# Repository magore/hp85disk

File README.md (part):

\section README

# Documentation
## HP85 Disk Emulator Copyright (C) 2014-2020 Mike Gore 
  * This Project Emulates **AMIGO** and **SS80** disk drives used by the **HP85** series computers.
  * The images are stored in **LIF** format used by the **HP85** series computers
  * See [COPYRIGHT](COPYRIGHT.md) for a full copyright notice for the project
  * Documentation created using Doxygen available at
    * https://rawgit.com/magore/hp85disk/master/doxygen/html/index.html
    * All emulated disk images are just regular files stored on a standard FAT32 formatted SD Card

## Features for the **HP85** in brief
  * **NOTE: Later sections go into more detail**
  * This project emulates **GPIB drives** and **HPGL printer**
    * Each emulated disk image is a **LIF** encoded file on a FAT32 formatted SD CARD.
    * **You MUST have the GPIB module installed in your HP85 in order to connect to the hp85disk emulator**
   * [sdcard/hpdisk.cfg](sdcard/hpdisk.cfg) fully defines each disk image on SD Card
     * Disk images are **LIF** encoded files that are compatible with **HP85A/B** and many other computers
     * Missing disk image files are created automatically if 
  * The emulator will automatically create missing **LIF** images defined in [sdcard/hpdisk.cfg](sdcard/hpdisk.cfg) on the SD CARD
  * There are disk images for **AMIGO** and **SS80** disks
    * **AMIGO** drives work with **HP85A** 
    * **SS80** drives work with **HP85B** (or **HP85A** with **PRM-85** with modified EMS and Electronic disk ROM add on board see links)
      * You may have up to 4 disks with V1 hardware and 8 with V2 hardware
  * There is a **Printer emulator** that can capture and save printer data to a time stamped file.
  * Built in command processor with lots of useful features
    * Want to translate between plain text **BASIC** files and **HP85** BASIC programs? You Can!
      * See full details later in this document
    * Access the hp85disk command processor via its USB interface and your computer with a serial terminal program
      * See full details later in this document for serial terminal configuration and finding the device port name
    * Any key press halts the emulator and waits for a user command
      * After finishing any user commend and options press the Enter/Return key to return to disk emulation
    * Type **help** for a list of top level commands
      * Each help item has its own help
      * Example: **lif help**
   * **LIF** manipulation tools are built in see later sections for details
   * Convert *TeleDisk* images into **LIF**
   * The emulator **RTC** can be used for time stamping plot files and files added into lif images

___ 

## Credits

## HP85 disk emulator V2 circuit board layout design by (C) 2018-2020 Jay Hamlin
## V2 board design - github master branch targets both old and new board by Jay Hamlin
## V2 code is now working
  * [Jay Hamlin designed this board](board/V2/releases)
  * V2 hardware adds
   * **PCB Circuit board design**
   * **GPIB BUS drivers**
     * 48Mma drive required by the GPIB spec
   * **I2C** level converters and standard Qwiic Bus interface - 3.3V
   * **RTC** clock for time stamping files added to **LIF** images, etc
   * Optional I2C LCD interface
     * work in progress
   * Advanced Hardware Reset circuit
   * Micro size SD card interface
  * [Current design files](https://github.com/magore/hp85disk/tree/master/board/releases/HP85Disk_release_03)
## V2 Pictures by Jay Hamlin

## HP85 disk emulator V1 board design (C) 2014-2020 Mike Gore
## [V1 board readme](board/V1/README.md)
  * [My original board design without **GPIB** buffers](board/V1/README.md)
  * Limited control and BUS drive power 
  * If you are using a **V1** board changes the update the [Makefile](Makefile) **BOARD ?= 1**
    * About half of the 48Mma drive required by the **GPIB** spec
    * However we can read any pin any time - useful for tracing/debugging
  * **RTC** -  **DS1307** for time stamping 

## HP Disk Emulator by Anders Gustafsson
**Anders Gustafsson was extremely helpful in getting my project started.**
*In fact I really owe the very existence of this project to his original project*
 * You can visit his project at this site:
   * <http://www.dalton.ax/hpdisk>
   * <http://www.elektor-labs.com/project/hpdisk-an-sd-based-disk-emulator-for-gpib-instruments-and-computers.13693.html>

Anders originally provided me his source code in 2014 and many details of his project *which I am very thankful for.*
NOTE: 
 I ended up rewriting virtually all of Anders project.
 This was mainly a personal exercise in fully understanding the code and NOT because of any problems with his original work.
 I did this one part at a time as I read the HP documents covering the protocols and specifications.
 Although rewritten I have maintained the basic concept of using  state machines for **GPIB** ,**AMIGO** and **SS80** state tracking.

## The HPDir project was a vital documentation source for this project
  * <http://www.hp9845.net/9845/projects/hpdir>
  * I use the **hpdir.ini** of their project for creating disk images

### Other HPDir resources for disk image manipulation
  * [HPDrive project has very useful references an tools for creating HP disk **LIF** images compatible with this project](http://www.hp9845.net/9845/projects/hpdrive)
    * Copyright © 2010 **A. Kückes**
  * [HPDir project has very useful references and tools for manipulating HP disk **LIF** images compatible with this project](http://www.hp9845.net/9845/projects/hpdrive)
    * Copyright © 2010 **A. Kückes**
  * [ See **LIF** Documentation - part of the HPDir project for details](http://www.hp9845.net/9845/projects/hpdir/#lif_filesystem)
    * Copyright © 2010 **A. Kückes**

## My TeleDisk to LIF conversion utility
 * I used the lzss libraries and documentation by **Dave Dunfield**
   * Copyright 2007-2008 Dave Dunfield All rights reserved.
 * Documentation from **Jean-Franois DEL NERO**
   * Copyright (C) 2006-2014 Jean-Franois DEL NERO
[lif/teledisk](lif/teledisk)
 * [lif/teledisk](lif/teledisk)
   * My **TELEDISK LIF** extractor
   * Important Contributions (My converted would not have been possible without these)
     * **Dave Dunfield**, LZSS Code and *TeleDisk* documentation
       * Copyright 2007-2008 Dave Dunfield All rights reserved.
       * [td0_lzss.h](lif/teledisk/td0_lzss.h)
       * [td0_lzss.c](lif/teledisk/td0_lzss.c)
         * *LZSS decoder*
       * [td0notes.txt](lif/teledisk/td0notes.txt)
         * *TeleDisk Documentation*
     * **Jean-Franois DEL NERO**, **TeleDisk Documentation**
       * Copyright (C) 2006-2014 Jean-Franois DEL NERO
         * [wteledsk.htm](lif/teledisk/wteledsk.htm)
           * *TeleDisk documentation*
         * See his github project
             * https://github.com/jfdelnero/libhxcfe

## FatFS low level disk IO
  * [fatfs](fatfs)
    * R0.14 FatFS code from (C) **ChaN**, 2019 - With very minimal changes 

## Optiboot
  * [optiboot](optiboot)
    * Optiboot Bootloader for Arduino and Atmel AVR
    * See: https://github.com/Optiboot/optiboot
       * [GPLv2 WRT](https://github.com/Optiboot/optiboot/blob/master/LICENSE)
       * [README](https://github.com/Optiboot/optiboot/blob/master/README.md)

## STK500v1 uploader for Optiboot
  * [uploader/flasher.py](uploader/flasher.py)
    * Optiboot uploader by **Mathieu Virbel** <mat@meltingrocks.com> 
      * Original repository https://github.com/tito/stk500
        * Authors main github page https://github.com/tito/stk500
          * https://meltingrocks.com/
  * Changes Jay and I made
   * Changed to atmega1284p
   * Jay converted code to Python 3
   * Added Baudrate argument
   * Added code to send "reset" command to hp85disk firmware to drop into optiboot
   * Fixed Intel 02 segment record calculation

___

## Resource Links 
  * 3D printed cases
    * https://github.com/MartinHepperle/HP-ReproParts

___

## Initial Setup of HP85 disk V2 PCB by Jay Hamlin
### Setup checklist
  * **You must an HP85 82937A GPIB card installed** [See document](Documents/82937AHP-IBInterface-InstallationAndTheoryOfOperationManual-82937-90007-56pages-Oct80)
    * **You must also have the required HP 82937A option roms installed**
      * **Mass Storage ROM** [Mass Storage ROM Manual](Documents/HP85-MassStorage.pdf)
      * **NOTE** I use the **PRM-85** with the HP85A super ROM - in my unit as it has all of the option ROMs included
  * Connect the GPIB plug from your HP85 GPIB card to the emulator - for initial testing make sure it is the only GPIB device attached
  * **NOTE:** The Emulator must be powered up and attached **before your HP85 is turned on** (the HP85 only detects disks after power-on or reset)
  * Attach the Power Supply with 2.1mm jack - suggest 7.5V to 9V DC regulated adapter with negative outside, positive center
    * You will see LED1 flash several times while the system is reading the configuration file and detecting disk images
    * If LED2 turns on there is an error reading the SD Card - see **SD Card problems** section

### Host computer requirements for serial debugging and firmware updating
  * You have either
    * **Ubuntu Linux desktop**
    * **Windows 10** running Windows Subsystem for Linux (Called WSL ) and the Ubuntu App from the Microsoft App store
    * **Mac OS**
  * All Text and configuration files used with the emulator MUST plain text format only (8 bit ASCII) 
     * Please NO Unicode - both file names and file formats!
  * You have a serial terminal program installed - for example minicom 
  * You need a FAT32 format blank SD Card
    * Copy of the hp85disk, github master branch, sdcard folder contents onto the SD Card
      * Make sure you only copy the contents and NOT folder AND contents
        * The emulator assumes the SD card home directory contains the images and configuration files

### Testing the emulator with the HP85
  * Turn on your HP85 - once the cursor is visable type the command **CAT**
    * You should see a directory listing, otherwise go to the bext section **initial troubleshooting**
  * If you have a directory listing see section called **HP85A and HP85B examples** for more examples

### Initial troubleshooting - if CAT gives a time-out error 
  * Make sure your device is the ONLY DEVICE attached to the HP 82937A controller of your HP85
  * You might not have the required option **ROMs** installed in your **HP85** for the HP85 GPIB interface card
  * The SD Card is missing the configuration file or disk images
  * The SD Card filesystem is corrupt.
  * See **SD Card problems** section
  * **NOTE** I would also suggest connecting your computer to the USB connector for more detailed disagnostics
  * USB Connection Summary
    * Attach USB cable from emulator to your computer using a serial terminal program
    * Read starting with section 
      * [Firmware updating and connecting to the hp85disk emulator with MINIMAL software install](#firmware-updating-and-connecting-to-the-hp85disk-emulator-with-minimal-software-install)
      * Read down to section [Connecting to hp85disk interactive serial port](#connecting-to-hp85disk-interactive-serial-port)
      * Read section [Command interface notes}(#command-interface-notes)
    * See section [hp85disk troubleshooting with serial terminal and DEBUG option](#hp85disk-troubleshooting-with-serial-terminal-and-debug-option) to verify your HP85 is communicating with your emulator
  * With the serial terminal connected type **help** you should see a help menu
    * To make sure there are files on the SD Card type one of these commands
      * **fatfs ls** for windows like director listing [example result](fatfs-ls.txt)  
      * **ls** for a Linux like directory listing [example result](trace/ls.txt)
  * Enter the serail terminal command **cat hpdisk.cfg** to see if you can read the main configuration file
  * Turn on debugging with the **DEBUG =** command
  * References
    * [hp85disk troubleshooting with serial terminal and DEBUG option](#hp85disk-troubleshooting-with-serial-terminal-and-debug-option)
    * [hp85disk DEBUG truth table](#hp85disk-debug-truth-table)
    * hp85disk setting debug examples](#hp85disk-setting-debug-examples)

### Status DEBUG LEDs
  * **LED2** goes on for error conditions - this is the LED nearest the GPIB connector
    * If this turns on you have an SDCARD problem - either missing card or filesystem issue
    * This LED will only go off after a reset and if no SD Card problems are detected
  * **LED1** is on when the SD Card is being read or written to

## Detailed information about tools and features 

## Built in command processor with many tools
### Accessing the hp85disk command interface with a serial terminal
  * Used to access the hp85disk command interface
  
### Command interface notes
  * When typing **any character** to the hp85disk emulator will stop disk emulation and display:
    * \<INTERRUPT>
  * After you type **Enter** the command processor will execute the command and return to disk emulation automatically

### Summary Getting files into and out of the emulator
  * The emulator uses a standard FAT32 formatted SD card accessable by standard Windows/Mac/Linux desktops.
    * This means you can removed the SD card and attach it to your desttop PC with a card reader
      * **ALWAYS POWER OFF the EMULATOR when inserting or removing the SD card**
  * Emulator disk images are single FAT32 files that are internally fomatted as LIF images - the format used by the HP85
  * This design allows you to copy files to/from the SD Card with your desktop PC
  * The hp85disk project includes tools for your desktop PC that can add/extract files from LIF disk images
    * These file and LIF image tools are also built into the emulator firmware - see references
      * [File manipulation commands built into the emulator](README.md#sd-card-file-manipulation-commands)
      * [LIF tools refrence](README.md#lif-tools-are-built-into-emulator-firmware)
      * [LIF - Importing TEXT files into LIF images](README.md#importing-ascii-and-plain-text-as-hp85-basic-programs)
      * [LIF - Exporting TEXT files from LIF images](README.md#exporting-hp85-basic-programs-to-ascii-plain-text)
      * [LIF - command](README.md#for-lif-help-type-lif-help)
    
___ 

## Important notes about SD Card requirements for the emulator

### Removing the SD Card from the emulator
  * **ALWAYS POWER OFF THE EMULATOR BEFORE REMOVING -or - INSERTING THE SD CARD**

### Formatting a new SD Card 
  * Must be formatted **FAT32** not FAT32x

### Using the SD Card images on your HP85
  * We provide the emulator with an SD card with images already installed
    * If you wish to create a new one follow these steps
  * There are working copies of disk images under the github sdcard folder
  * Open a web browser to https://github.com/magore/hp85disk
    * Click on the Green **Clone or Download** button
    * Pick download as **ZIP**
    * You can extract all of the folders and files to a folder of your choice
    * locate the **sdcard** folder
  * Copy the **contents** of the **sdcard** folder to the root/home folder of a a FAT32 formatted SD card
    * You should not see the **sdcard** folder on the SD Card itself just the contents of that folder and its subfolders

#### HP85A users SD card setup
  * Normally you will not be able to access **SS80** drives unless you have versions of the **HP85B** ROMS installed
    * See the notes about using a **PRM-85** to add the required ROMS
  * Copy the [amigo.cfg](sdcard/amigo.cfg) to the SD card and rename it to [hpdisk.cfg](sdcard/hpdisk.cfg)
    * This is an **AMIGO** drive only configuration
    * The default amigo.cfg file defines four **AMIGO** drives ready to go

#### HP85B users SD card setup
  * You needs the **EMS** ROM for **SS80** drives
    * If you do not have them see the **HP85A** notes above
  * You do not need to make any changes
    * The default [hpdisk.cfg](sdcard/hpdisk.cfg) uses two **AMIGO** drives and two **SS80** drives ready to go

___ 

###  Choosing an SD Card for the HP85 emulator PLEASE READ
  * Summary: When the hp85disk emulator writes to the SD Card the Card internally must modify a much much larger internal flash page - this can take too long
    * The **HP85** is sensitive to long read/write delays that some cards can cause problems with
    * You want SD Cards with fast random writes
    * I have found that the SanDisk Extreme and SanDisk Extreme Pro cards work best.
      * There is a huge difference in various cards on the market. 
      * Look for the cards with the best 4K random write times
      * A good source of benchmark information is looking for recent Raspberry Pi SD card benchmarks because they use SD Cards
        * Specifically look at best 4k random write - faster is better.
  * Details:
    * First step: hp85disk emulator writes to the SD Card
    * Internally the SD card finds an internal page where our data will go
    * Next the SD Card reads the page into internal RAM (recall it can be much over a megabyte)
    * Next the SD Card modifies the internal RAM with our data
    * Next the SD Card erases the page
    * Lastly the page is written to the SD Card and this takes time
      * Trivia - SD cards must to erase a page before updating because of the flash memory cell design
  * Why is this delay critical to the hp85disk emulator?
    * Too long of a delay can cause a timeout when writing to disk
    * SD cards internal hardware is mostly optimized for sequential writing 
      * Their buffers and timing are designed primarily for writing consecutive blocks one after another
        * When writing in consecutive order they can queue up many requests and combine them into one operation - a huge savings in time - done all in hardware
        * Writing to blocks in random locations break this optimization very badly
          * Therefore some SD Cards can take so long the **HP85** can timeout
      * The hp85disk emulator does not have enough memory to work around this issue
        * If we could load the entire disk image into ram AND we had more for many write buffers
          * Then we could optimize the SD Card writing process to avoid the problems
        * The AVR we use has only 20K of ram for everything
          * Perhaps some day we will port this project to a Raspberry PI with add on hardware
            * The protocol is already solved for the emulator so this would not be that hard - only a battle with the time I have free

### SD Card problems 
  * The the file system on the SD card might get corrupted if it was powered on while removing the card
    * **Symptoms - the hp85disk will not detect any drives**
      * This is because the small FatFS file system code I used can not self repair any filesystem errors
  * If you suspect this the easy way to check is to connect the emulator to a desktop/laptop computer
    * See [Firmware updating and connecting to the hp85disk emulator with MINIMAL software install](#firmware-updating-and-connecting-to-the-hp85disk-emulator-with-minimal-software-install)
  * When powering on the emulator it will report a details about the SD Card - you will see very obvious errors if it can not read the SD Card
  * If the emulator says it can not open the card then go to the **SD Card filesystem repair sections**

### SD Card filesystem repair
  * **Windows** insert the Micro SD card into you desktop/laptop Card Reader
    * Windows might detect errors and offer to fix them - answer **yes**
    * You can make Windows Check the drive using the following steps
      * Open *File Explorer* **Right Click** on the SD card drive and pick **properties**
      * Open the Tools tab
      * Click on Error Checking 
  * **Ubuntu Desktop with GUI** insert the Micro SD card into you desktop/laptop Card Reader
    * Under **Activities** search for **Disks**
      * Open **Disks** You will see a list of all of your drives on the left panel
        * Not - your SD Card may look like a USB device if you use a USB card reader
      * Click on the correct drive in the left panel
        * You will notice it give the size and partition type
      * Click on the Volume in the right panel
      * Click on the settings gear icon below the Volume
      * Click Repair filesystem
  * **Ubuntu Command line - without GUI** 
    * **sudo bash**
	* Method 1
      * Insert the Micro SD card into you desktop/laptop Card Reader
      * **dmesg | tail -25**
        * You will see the device partition listed in the last 10 or 20 lines
        * We will use: **/dev/sdc1** in the example **MAKE SURE YOU USE THE ONE YOU DETECTED**
      * **umount /dev/sdc1**
      * **fsck -f /dev/sdc1**
	* Method 2
    * **udevadm monitor --udev**
      * Insert the Micro SD card into you desktop/laptop Card Reader
      * The "add" lines will have the card partition listed on the far right
        * We will use: **/dev/sdc1** in the example **MAKE SURE YOU USE THE ONE YOU DETECTED**
      * Press **Ctrl c** to exit udevadm monitor
      * **umount /dev/sdc1**
      * **fsck -f /dev/sdc1**

___ 

## SD Card file manipulation commands 
  * **posix help** displays a list of these SD cards related commands
    * **NOTE: you do NOT have to put the "posix" keyword prior to any of these command**
  * These are very useful for backing up and copying disk images and configuration files
  * Path names may optionally be fully qualified file names or relative names
  * Directory seperators may be / or \
  * Relative names can include . or ..
    * Examples
       * .. is previous directory
       * .  is current directory
       * / or \ is a directory separator
       * /configs/../amigo0.lif is the same as /amigo0.lif
  * Note: Wild card pattern matching is NOT implemented on any of these commands.

### SD Card file command summary with examples
  * **cd dir**
    * Change to new working, default,  directory
<pre>
    cd /configs
</pre>

  * **pwd**
    * Display current working, default,  directory
<pre>
    pwd
    /configs
</pre>

  * **ls files and or directories**
    * You can specify any number of files or directory names or files as arguments
      * This is limited to a total length of 250 characters total
    * File information displayed includes type size date and name 
      * The file and directory information displayed is similar to the Linux **ls -la** command
    * Directory listing includes the file count for each directory
    * Example: 
<pre>
    ls /notes /backups /amigo0.lifg
    Listing:[/notes]
    -rwxrwxrwx none none         4151 Mon Mar  2 00:19:16 2020 drive-parameters.txt
    -rwxrwxrwx none none          563 Sun Mar  1 22:19:48 2020 GETSAVE-Readme.txt
    -rwxrwxrwx none none       367277 Sun Mar  1 22:08:44 2020 GETSAV Series80 Group Data Communications Pac for the HP 83_85.pdf
    -rwxrwxrwx none none       312128 Sun Mar  1 22:09:48 2020 GETSAV Series80 Group HP85 I_O rom Image specifier error 52.pdf
    -rwxrwxrwx none none         2560 Sun Mar  1 03:57:42 2020 GETSAVE.#e008
    -rwxrwxrwx none none         3512 Sat Feb 29 07:19:34 2020 drives_parameters.txt
    -rwxrwxrwx none none          102 Sun Mar  1 07:20:12 2020 hpdir-notes-examples.txt
    Files: 7
    Listing:[/backups]
    -rwxrwxrwx none none         3416 Fri Dec 31 19:17:44 1999 amigo.cfg
    -rwxrwxrwx none none         5690 Fri Dec 31 19:18:00 1999 hpdisk.cfg
    Files: 2
    Listing:[/amigo0.lif]
    -rwxrwxrwx none none       286720 Mon Apr 13 00:03:22 2020 amigo0.lif
    Files: 1
</pre>
  * **mkdir dir**
    * Make a new directory called dir
  * **rmdir dir**
    * Delete a directory - it must be empty
  * **rm file**
    * Remove/Delete a file
  * **copy file1 file2**
    * Copy an existing file to a new location and name
<pre>
	mkdir /backups
	copy /amigo.cfg /backups/amigo.cfg
    Opening /amigo.cfg
    Creating /backups/amigo.cfg
    
    Copying...
    3416 bytes copied.
    
    copy /hpdisk.cfg /backups/hpdisk.cfg
    Opening /hpdisk.cfg
    Creating /backups/hpdisk.cfg
    
    Copying...
    5690 bytes copied.
</pre>
  * **rename old new**
    * Rename a file - this is similar to a move command source and destination paths and names can differ
  * **page NN**
   * **NN** is the number of lines to display per page with the **cat** with the page **-p** option
   * Default is 25 lines
  * **cat file [-p]**
    * List a file to the display with optional pausing
    * **-p** page option tells **cat** to pause after the number of lines specified by the **page** command
    * When pausing, typing Space advances another page, Enter another line, q exits

___ 

## LIF tools are built into emulator firmware 
  * Built in help
    * **lif help**
      * Gives lif commands
  * Summary - List, Create, import, export, translate, copy, rename, delete, etc
  * NOTE: Each disk image is a single file, encoded in **LIF** format, saved on the SD Card
    * **LIF** format is a common the filesystem on series 80 computers.
    * **LIF** format is also a vary common file interchange format for series 80 computers
      * **LIF** format includes file date, size permissions and other important meta data
  * Translate between DTA8x (type E010) and plain text files
      * You can add a plain text file, and translate it, into a **LIF** image with file format DTA8x (type E010)
      * You can extract and translate DTA8x (type E010) into a plain text files
  * **Key LIF manipulation features**
    * **dir** display a directory of a **LIF** image
      * Directory listing of **LIF** images and SD Card files
      * If you have an RTC the listing can display file and **LIF** volume date and time
        * Display time stamps if they were set
          * But only if they were created or added with the built in tools
    * **add** an ascii file to **LIF** image
      * This function permits renaming of the translated file
      * They get translated between **HP85** DTA8x (type E010) format and plain text files!!!
    * **extract** ASCII files from **LIF** image
      * This function permits renaming of the translated file
      * They get translated between **HP85** DTA8x (type E010) format and plain text files!!!
    * **addbin** add binary programs from one **LIF** image to another *LIF* image
      * This function permits renaming of the translated file
    * **extractbin** a single binary file or program into a new **LIF** image
      * This function permits renaming of the translated file
      * Extracted **LIF** images contain a single file a 256 byte volume header, 256 byte directory followed by a file.
    * **del** delete file in **LIF** image
    * **rename** file in **LIF** image
    * **create** create a LIF image specifying a label, directory size and overall disk size
    * **createdisk** create a LIF image specifying a label and drive model name
  * [For more **LIF** documentation](lif/README.md)

## TeleDisk to LIF conversion tool (updated) - see [LIF README.md](lif/README.md)
  * [td02lif](lif/t202lif) [85-SS80.TD0](lif/85-SS80.TD0) [85-SS80.LIF](lif/85-SS80.LIF)
  * NOTE: There are a stand alone version of the tool that run on Linux - making it work on Windows should be easy
      * You can extract a **DTA8x** (type E010) file from a **LIF** image and translate it into plain text
  * TeleDisk to **LIF** image conversion - a very common disk interchange format
    * See the top of [lifutils.c](lif/lifutils.c) for full documentation and examples.
    * create **LIF** image with options
    * NOTE: the emulator automatically creates missing images if defined in [sdcard/hpdisk.cfg](sdcard/hpdisk.cfg)
      * Type "lif help" in the emulator for a full list of commands
      * See the top of [lifutils.c](lif/lifutils.c) for full documentation and examples.

## Disk images and default configuration file for the hp85disk project
  * [sdcard folder has premade **LIF** disk images](sdcard)
    * [sdcard/create_images.sh](sdcard/create_images.sh)  creates the default **LIF** images and creates a matching default configuration files
  * [sdcard/hpdisk.cfg](sdcard/hpdisk.cfg) contains the default disk definitions that correspond to the **LIF** images - disk hardware definition
    * NOTE: The file paths can include subdirectory paths in the file name. This permits using multiple folders

## Note about LIF images and [sdcard/hpdisk.cfg](sdcard/hpdisk.cfg) disk definitions
  * To create/modify or update **LIF** images see the section on the LIF utilities supplied with the emulator
  * It is important that the **LIF** image size match the disk definitions
    * The emulator gets the hard limits for  disk using [sdcard/hpdisk.cfg](sdcard/hpdisk.cfg)
      * The attached computer requests these disk details from the emulator 
    * Then the attached computer reads the disk **LIF** headers for the *LIF* layout information. 
      * So as long as the **LIF** headers and hardware information match things should work fine.
        * IF the do not match you may get errors when
          * If the **LIF** image is BIGGER then specified disk AND if the computer attempts to read outside the defined limits.
  * The emulator does not look at the **LIF** data when serving and image - that is up to the attached computer.
   * The computer also gets the disk description from the emulator when it scans for disks

___ 

## Specific details for Translating between plain text and HP85 BASIC programs using hp85disk
  * Requirements
    * hp85disk emulator 
      * There is a solution documented below in you do not have the hp85emulator
    * A HP utility commonly called "GETSAV" translates between **HP85** BASIC and DTA8x (type E010) files
      * The utility adds functions "GET" and "SAVE" to your **HP85** computer
        * This HP utility was part of a larger software package from HP for the **HP85**

## GETSAV is called GETSAVE inside my LIF disk images
  * Here is a direct link to *GETSAVE.LIF* - which is encoded as a **LIF** file: [sdcard/LIF-files/GETSAVE.LIF](sdcard/LIF-files/GETSAVE.LIF)
    * Can be installed on the **HP85** with using **LOADBIN "GETSAVE"**
  * My hp85disk tools built in the firmware can tools translate between DT8x (type E010 ) and plain text ASCII files
    * I provide stand alone **LIF** tools in the lif subfolder of the github project that do the same thing
  * Used together with the **HP85** these tools can translate between ASCII plain text and *HP85* BASIC programs!!!
    * Specific details steps are documented later in the README

## Translating between plain text and HP85 BASIC programs WITHOUT hp85disk
  * You must compile and install the stand alone lif tools found under the project [lif](lif) folder
  * You will also need a way of transfer binary files to/from your **HP85** 
    * You need to copy the **GETSAVE** program to your **HP85** some how
  * Specific details steps are documented later in the README

___ 

## FULL example step by step translating bewteen plain text files and HP85 BASIC programs
  * You can do these examples without out my emulator but requires an extra tools and steps

## Importing ASCII and plain text as HP85 BASIC programs
  * Lets import a text file with BASIC statements into one of the emulator images **amigo1.lif**
  * Turn off both the **HP85** and emulator - if it is attached
    * Remove the SD Card
  * Create a plain text file with BASIC statements in it **on your Desktop - NOT on HP85**
      * **10 DISP "HELLO WORLD"**
      * **20 END**
    * Save this file as **TEST.txt** onto the SD Card and exit your editor 
      * umount the SD Card "eject it" in windows jargon
      * Reinstall the SD Card in the emulator
  * Turn on the hp85disk emulator FIRST - THEN turn on the **HP85**
    * Trivia - the **HP85 only detects disk at power on or after a RESET** 
      * **Therefore the emulator MUST be running first**
    * Open your serial program with the documented settings

  * Lets add **TEST.txt** from the SD Card into the **amigo1.lif** emulator disk image
    * Type:
      * **lif add amigo1.lif TEST TEST.txt**
        * **TEST** is the internal **LIF** name, **TEST.txt** is you source file

  * On your **HP85** we will load a binary program called **GETSAVE**
    * **LOADBIN "GETSAVE"**
      * Note: quotes are always required on **HP85** BASIC file names
      * This installs **GETSAVE** into program memory on your **HP85** until reset or power cycle
        * **GETSAVE** adds new functions **"GET"** and **"SAVE"** to your **HP85** computer
  * On the **HP85** type
    * **GET "TEST"**
      * Wait until you see **DONE**
        * On BIG programs GET can take a very long time 
          * The slow speed is a **GETSAVE** limitation and not due to my emulator speed
    * Lets save it as a normal **HP85** basic program
      * **STORE "TESTB"**
        * Saving in this format makes a totally HUGE difference in speed for BIG programs
        * In the future you can use **LOAD "TESTB"**

## Exporting HP85 BASIC programs to ASCII plain text
  * You must have the hp85disk emulator power ON and attached to you **HP85**
    * Turn on the **HP85**
  * On your **HP85** we will load a binary program called **GETSAVE**
    * **LOADBIN "GETSAVE"**
      * Note: quotes are always required on **HP85** BASIC file names
      * This installs **GETSAVE** into program memory on your **HP85** until reset or power cycle
        * **GETSAVE** adds new functions **"GET"** and **"SAVE"** to your **HP85** computer
  * Lets load a normal **HP85** BASIC program
    * **LOAD "RWTESTB"**
  * First stage conversions
    * **SAVE "RWTESTA"**
      * Wait until you see **DONE**
        * On BIG programs SAVE can take a very long time 
          * The slow speed is a **GETSAVE** limitation and not due to my emulator speed
  * Lets export and convert **"RWTESTA"** to plain text using the emulator command prompts
    * Type:
      * **lif extract amigo1.lif RWTESTA RWTEST.txt**
        * **TEST** is the internal **LIF** name, **TEST.txt** is you source file
      * This saves the file **RWTEST.txt** to the SD Card and plain text ASCII
    * Later you can copy the **RWTEST.txt** file to your desktop
      * Turn off the **HP85** and the emulator
      * Remove the SD Card
      * Attach to your desktop and copy it off

___ 

## Tested Operating systems
### Linux
  * I used **Ubuntu 18.04,16.04LTS and 14.04LTS** when developing the code
  * I have instructions for flashing the firmware below
### Windows
  * **Windows 10** running Windows Subsystem for Linux (Called WSL ) and the Ubuntu App from the Microsoft App store
-OR-
  * **Windows 10** with the Python 3.7 Microsoft App store

___ 

## Firmware updating and connecting to the hp85disk emulator with MINIMAL software install
  * **NOTE: The examples below refer to files that are part of this hp85disk project**
  * You need the following files **listports.py, flasher.py and gpib.hex** - here are the links
    * https://raw.githubusercontent.com/magore/hp85disk/master/uploader/listports.py
    * https://raw.githubusercontent.com/magore/hp85disk/master/uploader/flasher.py
    * https://raw.githubusercontent.com/magore/hp85disk/master/release/build/gpib.hex
  * **Please update any paths to suit where you download them to**

## Software requirments
### Linux
  * **apt-get install python3**
    * Most modern Linux systems have Python3
  * **pip3 install pySerial**

### Windows
  * Windows - Install Python 3.7 from Windows App Store
  * Note: if the python install fails to run and you get an error **VCRUNTIME140.dll**
    * You have a problem with the Visual C++ runtime files 
    * For a solution: https://www.winhelponline.com/blog/fix-vcruntime140-dll-missing-error-windows/
  * Open Power Shell window - always use Power Shell under Windows for running Python3
    * **pip3 install pySerial**

### Windows users that have an external ISP
  * You can also follow the notes under [release/build/windows/README.md](release/windows/README.md)
  * [release/windows](release/windows) includes avrdude and the required scripts for minimal flashing of the firmware
   
## Discover your serial port name
  * Make sure you have a mini usb cable handy
  * **Make sure the emulator mini-usb cable is NOT connected to your PC/Mac yet**
  * **Make sure the hp85disk is powered on**

### Linux
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
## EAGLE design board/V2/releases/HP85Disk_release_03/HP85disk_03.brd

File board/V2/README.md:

## Jay Hamlin V2 circuit board design 
  * Jay start work on this design about a year ago in 2019 
    * I only recently got around to updating my code to work with the new design. I am thankful of his contribution as it will allow more people to use build this project. After several exchanges Jay added GPIB drivers, New Parallel Poll circuit, and an I2C connector -for Real Time clock and and a future optional display. The GPIB drivers and and updated Parallel Poll circuit should allow using the drive with more devices attached on the GPIB BUS.
  * [Release folder has Eagle design files, PDF renderings and images of the board](releases)
    * Note: Eagle design software is (C) by Autodesk 

___

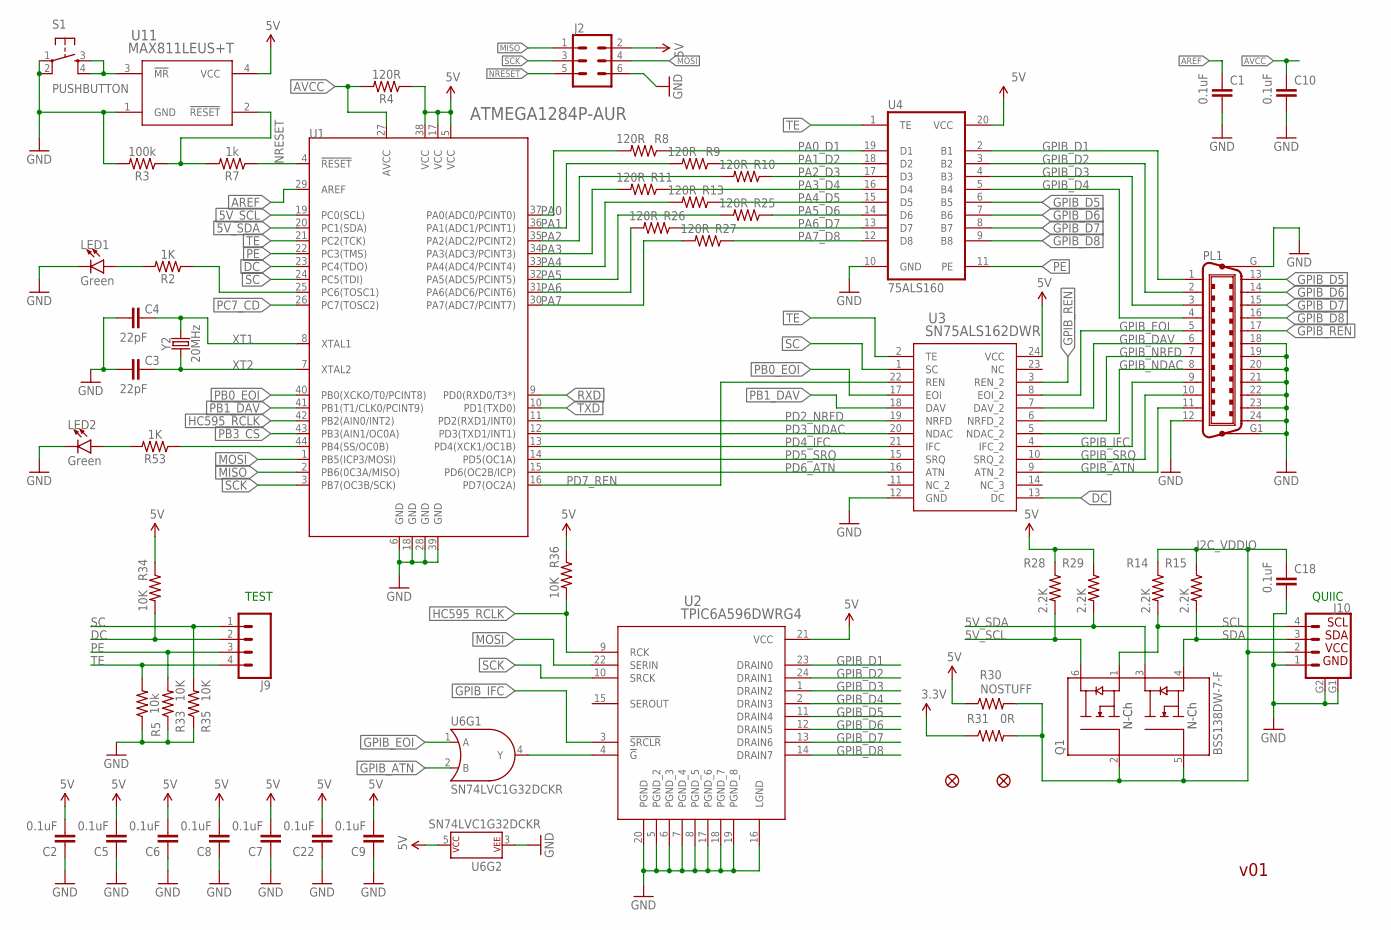
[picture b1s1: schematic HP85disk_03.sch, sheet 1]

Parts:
C1, C2, C5, C6, C7, C8, C9, C10, C18, C22: 0.1uF; 0603
C3, C4: 22pF; 0603
J2: CONN_03X2_BIGPADSFEMALE_SMD; 2X3_SMD
J9: CONN_041.27MM; 1X04_1.27MM
J10: QWIIC_CONNECTORJS-1MM; QUIIC_1X04_1MM_RA
JP8, JP9: FIDUCIAL1X2; FIDUCIAL-1X2
LED1, LED2: Green; LED-1206
PL1: C24HP; 24HP
Q1: BSS138DW-7-F; SOT-363
R2, R53: 1K; 0603
R3: 100k; 0603
R4, R8, R9, R10, R11, R13, R25, R26, R27: 120R; 0603
R5: 10k; 0603
R7: 1k; 0603
R14, R15, R28, R29: 2.2K; 0603
R30: NOSTUFF; 0603
R31: 0R; 0603
R33, R34, R35, R36: 10K; 0603
S1: PUSHBUTTON; TACTILE-SWITCH-SMD
U1: ATMEGA1284P-AUR; TQFP44
U2: TPIC6A596DWRG4; DW24
U3: SN75ALS162DWR; DW24
U4: 75ALS160; SO20L
U6: SN74LVC1G32DCKR; SOT23-5
U11: MAX811LEUS+T; 21-0052F
Y2: 20MHz; CRYSTAL-SMD-5X3.2-4PAD

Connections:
3.3V: R31.1; also elsewhere on the board
5V: C2.2, C5.2, C6.2, C7.2, C8.2, C9.2, C22.2, J2.2, R4.1, R28.1, R29.1, R30.1, R34.1, R36.1, U1.5 (VCC), U1.17 (VCC), U1.38 (VCC), U2.21 (VCC), U3.24 (VCC), U4.20 (VCC), U6.5 (P$V+), U11.4 (VCC); also elsewhere on the board
5V_SCL: Q1.6 (D1), R28.2, U1.19 (PC0(SCL)); also elsewhere on the board
5V_SDA: Q1.3 (D2), R29.2, U1.20 (PC1(SDA)); also elsewhere on the board
AREF: C1.1, U1.29 (AREF)
AVCC: C10.1, R4.2, U1.27 (AVCC)
DC: J9.2, R34.2, U1.23 (PC4(TDO)), U3.13 (DC)
GND: C1.2, C2.1, C3.1, C4.1, C5.1, C6.1, C7.1, C8.1, C9.1, C10.2, C18.2, C22.1, J2.6, J10.1, J10.G1, J10.G2, LED1.C, LED2.C, PL1.12, PL1.18, PL1.19, PL1.20, PL1.21, PL1.22, PL1.23, PL1.24, PL1.G, PL1.G1, R3.2, R5.1, R33.1, R35.1, S1.1, S1.2, U1.6 (GND), U1.18 (GND), U1.28 (GND), U1.39 (GND), U2.5 (PGND_2), U2.6 (PGND_3), U2.7 (PGND_4), U2.8 (PGND_5), U2.16 (LGND), U2.17 (PGND_6), U2.18 (PGND_7), U2.19 (PGND_8), U2.20 (PGND), U3.12 (GND), U4.10 (GND), U6.3 (P$V-), U11.1 (GND); also elsewhere on the board
GPIB_ATN: PL1.11, U3.9 (ATN_2), U6.2 (B)
GPIB_D1: PL1.1, U2.23 (DRAIN0), U4.2 (B1)
GPIB_D2: PL1.2, U2.24 (DRAIN1), U4.3 (B2)
GPIB_D3: PL1.3, U2.1 (DRAIN2), U4.4 (B3)
GPIB_D4: PL1.4, U2.2 (DRAIN3), U4.5 (B4)
GPIB_D5: PL1.13, U2.11 (DRAIN4), U4.6 (B5)
GPIB_D6: PL1.14, U2.12 (DRAIN5), U4.7 (B6)
GPIB_D7: PL1.15, U2.13 (DRAIN6), U4.8 (B7)
GPIB_D8: PL1.16, U2.14 (DRAIN7), U4.9 (B8)
GPIB_DAV: PL1.6, U3.7 (DAV_2)
GPIB_EOI: PL1.5, U3.8 (EOI_2), U6.1 (A)
GPIB_IFC: PL1.9, U2.3 (!SRCLR), U3.4 (IFC_2)
GPIB_NDAC: PL1.8, U3.5 (NDAC_2)
GPIB_NRFD: PL1.7, U3.6 (NRFD_2)
GPIB_REN: PL1.17, U3.3 (REN_2)
GPIB_SRQ: PL1.10, U3.10 (SRQ_2)
HC595_RCLK: R36.2, U1.42 (PB2(AIN0/INT2)), U2.9 (RCK)
I2C_VDDIO: C18.1, J10.2, Q1.2 (G1), Q1.5 (G2), R14.1, R15.1, R30.2, R31.2
MISO: J2.1, U1.2 (PB6(0C3A/MISO)); also elsewhere on the board
MOSI: J2.4, U1.1 (PB5(ICP3/MOSI)), U2.22 (SERIN); also elsewhere on the board
unnamed: R2.1, U1.25 (PC6(TOSC1))
unnamed: U2.4 (!G), U6.4 (Y)
unnamed: S1.3, S1.4, U11.3 (!MR)
unnamed: R53.1, U1.44 (PB4(SS/OC0B))
unnamed: R3.1, R7.2, U11.2 (!RESET)
unnamed: LED1.A, R2.2
unnamed: LED2.A, R53.2
NRESET: J2.5, R7.1, U1.4 (!RESET)
PA0: R8.2, U1.37 (PA0(ADC0/PCINT0))
PA0_D1: R8.1, U4.19 (D1)
PA1: R9.2, U1.36 (PA1(ADC1/PCINT1))
PA1_D2: R9.1, U4.18 (D2)
PA2: R10.2, U1.35 (PA2(ADC2/PCINT2))
PA2_D3: R10.1, U4.17 (D3)
PA3: R11.2, U1.34 (PA3(ADC3/PCINT3))
PA3_D4: R11.1, U4.16 (D4)
PA4: R13.2, U1.33 (PA4(ADC4/PCINT4))
PA4_D5: R13.1, U4.15 (D5)
PA5: R25.2, U1.32 (PA5(ADC5/PCINT5))
PA5_D6: R25.1, U4.14 (D6)
PA6: R26.2, U1.31 (PA6(ADC6/PCINT6))
PA6_D7: R26.1, U4.13 (D7)
PA7: R27.2, U1.30 (PA7(ADC7/PCINT7))
PA7_D8: R27.1, U4.12 (D8)
PB0_EOI: U1.40 (PB0(XCKO/T0/PCINT8)), U3.17 (EOI)
PB1_DAV: U1.41 (PB1(T1/CLK0/PCINT9)), U3.18 (DAV)
PB3_CS: U1.43 (PB3(AIN1/OC0A)); also elsewhere on the board
PC7_CD: U1.26 (PC7(TOSC2)); also elsewhere on the board
PD2_NRFD: U1.11 (PD2(RXD1/INT0)), U3.19 (NRFD)
PD3_NDAC: U1.12 (PD3(TXD1/INT1)), U3.20 (NDAC)
PD4_IFC: U1.13 (PD4(XCK1/OC1B)), U3.21 (IFC)
PD5_SRQ: U1.14 (PD5(OC1A)), U3.15 (SRQ)
PD6_ATN: U1.15 (PD6(OC2B/ICP)), U3.16 (ATN)
PD7_REN: U1.16 (PD7(OC2A)), U3.22 (REN)
PE: J9.3, R33.2, U1.22 (PC3(TMS)), U4.11 (PE)
RXD: U1.9 (PD0(RXD0/T3*)); also elsewhere on the board
SC: J9.1, R35.2, U1.24 (PC5(TDI)), U3.1 (SC)
SCK: J2.3, U1.3 (PB7(OC3B/SCK)), U2.10 (SRCK); also elsewhere on the board
SCL: J10.4, Q1.1 (S1), R14.2
SDA: J10.3, Q1.4 (S2), R15.2
TE: J9.4, R5.2, U1.21 (PC2(TCK)), U3.2 (TE), U4.1 (TE)
TXD: U1.10 (PD1(TXD0)); also elsewhere on the board
XT1: C4.2, U1.8 (XTAL1), Y2.3 (2)
XT2: C3.2, U1.7 (XTAL2), Y2.1

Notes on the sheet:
v01
TEST
QUIIC

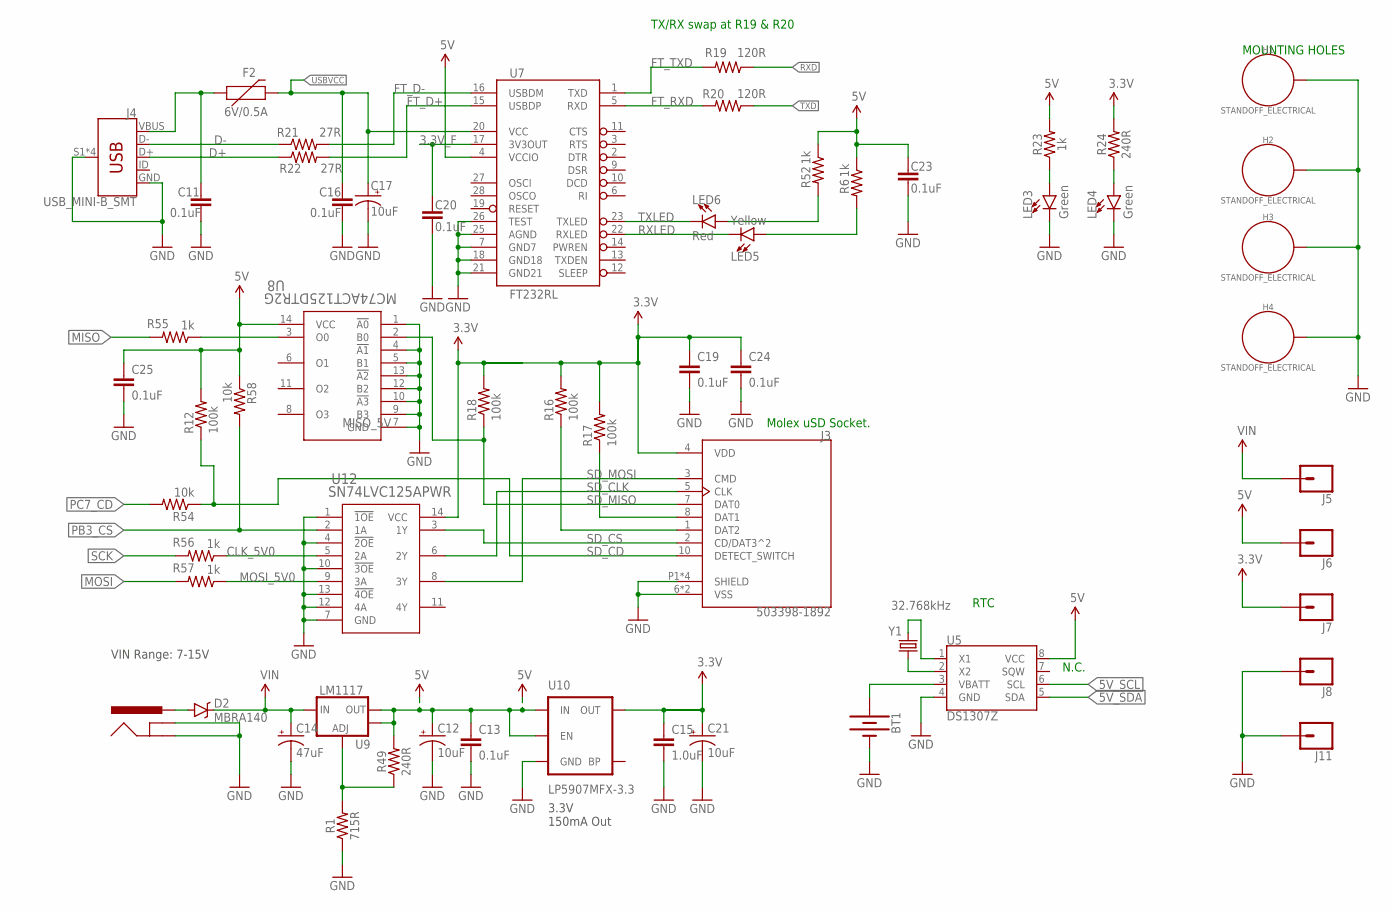
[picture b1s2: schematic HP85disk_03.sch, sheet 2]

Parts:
BT1: BATTERY-12MM_PTH; BATTCON_12MM_PTH
C11, C13, C16, C19, C20, C23, C24, C25: 0.1uF; 0603
C12, C17, C21: 10uF; EIA3216
C14: 47uF; PANASONIC_D
C15: 1.0uF; 0603
D2: MBRA140; SMA-DIODE
F2: 6V/0.5A; 1206
H1, H2, H3, H4: STANDOFF_ELECTRICAL; STANDOFF-ELECTRICAL
J1: POWER_JACKSUPER_BOMB_DIGITY; POWER_JACK_SMD_OVERPASTE_SUPER_BOMB_DIGITY
J3: 503398-1892; MOLEX_503398-1892
J4: USB_MINI-B_SMT; USB-MINIB
J5, J6, J7, J8, J11: CONN_01; 1X01
LED3, LED4: Green; LED-1206
LED5: Yellow; LED-1206
LED6: Red; LED-1206
R1: 715R; 0603
R6, R23, R52: 1k; 0603
R12, R16, R17, R18: 100k; 0603-RES
R19, R20: 120R; 0603
R21, R22: 27R; 0603
R24, R49: 240R; 0603
R54, R58: 10k; 0603-RES
R55, R56, R57: 1k; 0603-RES
U5: DS1307Z; SO08-0.15
U7: FT232RL; SSOP28DB
U8: MC74ACT125DTR2G; TSSOP14_4P50X5P10
U9: LM1117; SOT223-ALT1
U10: LP5907MFX-3.3; SOT23-5
U12: SN74LVC125APWR; PW14
Y1: 32.768kHz; CRYSTAL-SMD-2X6-CYL

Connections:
3.3V: C15.1, C19.1, C21.+, C24.1, J3.4 (VDD), J7.1, R16.2, R17.2, R18.2, R24.2, U10.5 (OUT), U12.14 (VCC); also elsewhere on the board
3.3V_F: C20.1, U7.17 (3V3OUT)
5V: C12.+, C13.1, C23.1, C25.1, J6.1, R6.1, R12.2, R23.2, R49.2, R52.1, R58.1, U5.8 (VCC), U7.4 (VCCIO), U8.14 (VCC), U9.2 (OUT), U9.4 (OUT), U10.1 (IN), U10.3 (EN); also elsewhere on the board
5V_SCL: U5.6 (SCL); also elsewhere on the board
5V_SDA: U5.5 (SDA); also elsewhere on the board
CLK_5V0: R56.1, U12.5 (2A)
D+: J4.D+, R22.1
D-: J4.D-, R21.1
FT_D+: R22.2, U7.15 (USBDP)
FT_D-: R21.2, U7.16 (USBDM)
FT_RXD: R20.2, U7.5 (RXD)
FT_TXD: R19.2, U7.1 (TXD)
GND: BT1.GND (-), C11.2, C12.-, C13.2, C14.-, C15.2, C16.2, C17.-, C19.2, C20.2, C21.-, C23.2, C24.2, C25.2, H1.P1, H2.P1, H3.P1, H4.P1, J1.GND (GNDBREAK), J1.P$4 (GND), J3.6 (VSS), J3.9 (VSS), J3.P1 (SHIELD), J3.P2 (SHIELD), J3.P3 (SHIELD), J3.P4 (SHIELD), J4.GND, J4.S1 (SHIELD), J4.S2 (SHIELD), J4.S3 (SHIELD), J4.S4 (SHIELD), J8.1, J11.1, LED3.C, LED4.C, R1.1, U5.4 (GND), U7.7 (GND7), U7.18 (GND18), U7.21 (GND21), U7.25 (AGND), U7.26 (TEST), U8.1 (!A0), U8.4 (!A1), U8.5 (B1), U8.7 (GND), U8.9 (B3), U8.10 (!A3), U8.12 (B2), U8.13 (!A2), U10.2 (GND), U12.1 (!1OE), U12.4 (!2OE), U12.7 (GND), U12.10 (!3OE), U12.12 (4A), U12.13 (!4OE); also elsewhere on the board
MISO: R55.2; also elsewhere on the board
MISO_5V: R55.1, U8.3 (O0)
MOSI: R57.2; also elsewhere on the board
MOSI_5V0: R57.1, U12.9 (3A)
unnamed: R1.2, R49.1, U9.1 (ADJ)
unnamed: LED6.A, R52.2
unnamed: LED3.A, R23.1
unnamed: LED5.A, R6.2
unnamed: J3.8 (DAT1), R17.1
unnamed: J3.1 (DAT2), R16.1
unnamed: U5.1 (X1), Y1.X2 (2)
unnamed: BT1.VCC@1 (+), U5.3 (VBATT)
unnamed: U5.2 (X2), Y1.X1 (1)
unnamed: LED4.A, R24.1
PB3_CS: R58.2, U12.2 (1A); also elsewhere on the board
PC7_CD: R54.2; also elsewhere on the board
PWRIN1: D2.A, J1.VIN0 (PWR)
RXD: R19.1; also elsewhere on the board
RXLED: LED5.C, U7.22 (RXLED)
SCK: R56.2; also elsewhere on the board
SD_CD: J3.10 (DETECT_SWITCH), R12.1, R54.1
SD_CLK: J3.5 (CLK), U12.6 (2Y)
SD_CS: J3.2 (CD/DAT3^2), U12.3 (1Y)
SD_MISO: J3.7 (DAT0), R18.1, U8.2 (B0)
SD_MOSI: J3.3 (CMD), U12.8 (3Y)
TXD: R20.1; also elsewhere on the board
TXLED: LED6.C, U7.23 (TXLED)
USBVCC: C16.1, C17.+, F2.2, U7.20 (VCC)
VIN: C14.+, D2.C, J5.1, U9.3 (IN)
VUSB1: C11.1, F2.1, J4.VBUS

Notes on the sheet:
3.3V 150mA Out
VIN Range: 7-15V
MOUNTING HOLES
TX/RX swap at R19 & R20
Molex uSD Socket.
N.C.
RTC

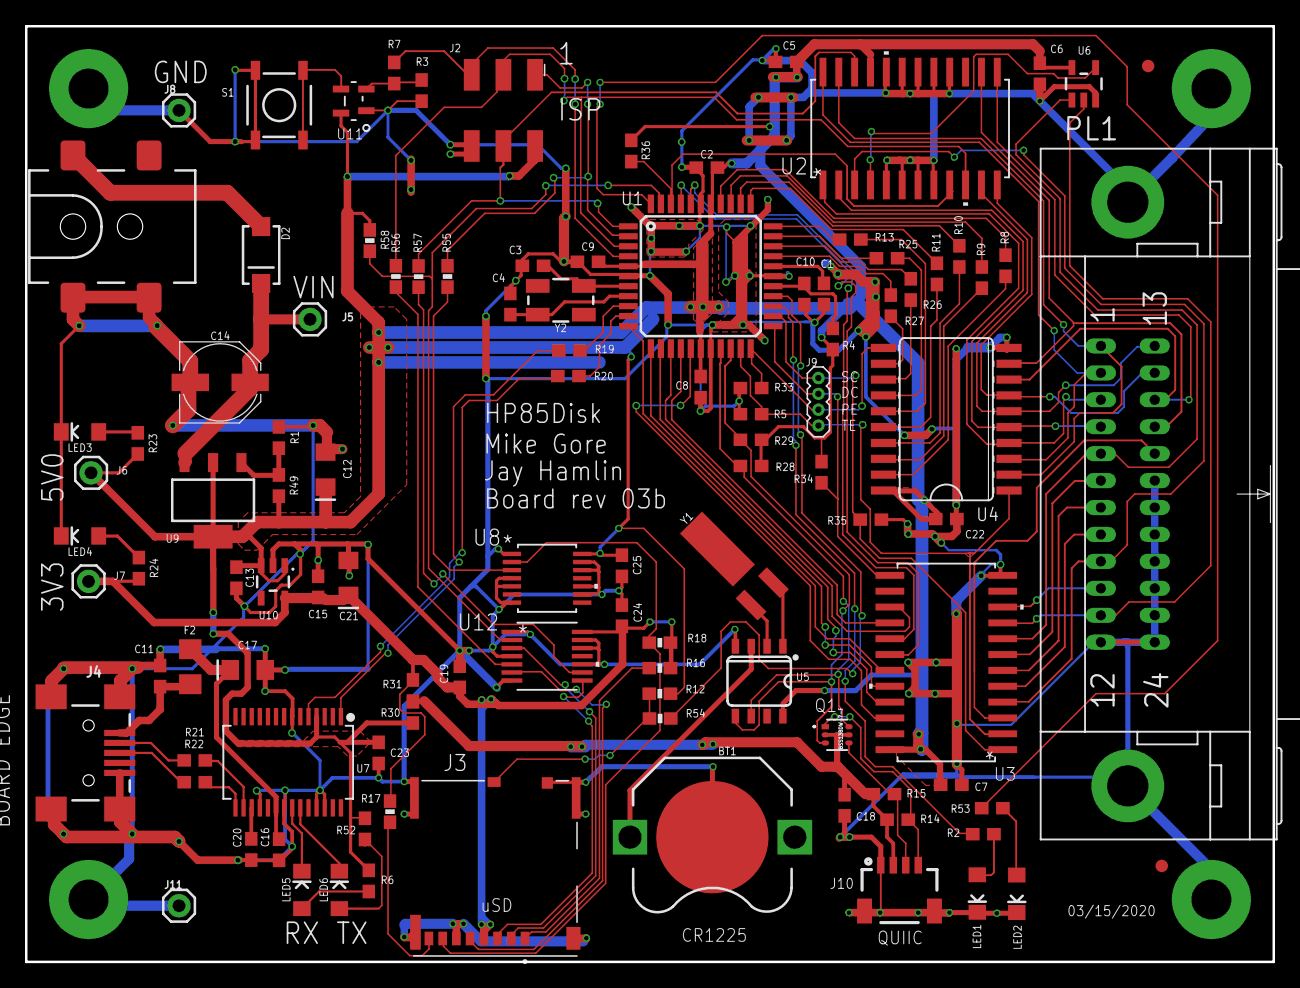
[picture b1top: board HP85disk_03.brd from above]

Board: 2 copper layers, 100.0 x 75.0 mm, 111 parts (0 on the bottom side), 103 nets.

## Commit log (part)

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2017-07-13 updated gpib read/write byte code - can now send requests to HP scope
2017-07-15 Display warnings for invalid (non-zero) unit and volume numbers for SS80 and AMIGO drives
2017-07-15 minor adjustments to gpib_read_byte and gpib_write_byte
2017-07-17 Added ofline copy of HPdir GPIB protocol notes, added controller mode functions
2017-07-28 Adding GPIB controller mode, Added TeleDisk to LIF conversion stand alone code
2017-07-28 Added compiling notes to README files
2017-07-29 Cleanup of README.md and lif/README.txt
2017-07-30 README.md added minicom to onstall notes
2017-08-02 LIF utilities now compile under MingW - MingW must have MSYS tools
2017-08-06 updated td02lif.c - working on imroving conversion of images with errors in them
2017-08-13 Updated TeleDisk summary write size to HEX
2017-08-13 lif/README.txt added url
2017-08-13 README.md formatting
2017-08-13 Renamed lif/README.txt and lif/teledisk/README.txt to .md extensions
2017-08-13 updated lif/teledisk/README.md
2017-08-13 Added teledisk conversion example to lif/README.md
2017-08-13 Added TeleDisk LIF extractor note to Features section of README.md
2017-08-13 Updated all help menus - help from emulator only list the top level help for each subsystem
2017-08-19 README.md, COPYRIGHT.md, lif/README.md Copyright symbol update
2017-08-19 READE.md update
2017-08-29 Rewrote TeleDisk LIF analasis code for robust detection
2017-09-15 Fixed two errors when compiling lif and td02lif under MING32
2017-09-15 Fixed two errors with compiling lif and td02lif under MING32
2020-02-12 Added Jay Hamlin circuit board files for V2
2020-02-12 updated braches correctly
2020-02-13 README update
2020-02-16 Updated board files to 15 Feb 2020 release by Jay Hamlin
2020-02-16 Updated board release folder structure
2020-02-16 README
2020-02-16 fixing links
2020-02-16 README links
2020-02-16 Documentation updates
2020-02-16 Documnation link fixes
2020-02-17 Update Doxygen files
2020-02-17 fixing doxygen links
2020-02-17 Fixed doxygen generation script
2020-02-17 doxygen updates
2020-02-17 Dxygen updates
2020-02-18 Documentation formatting
2020-02-18 Updated project V1 pictures
2020-02-18 Added README.md to board/V2 for Jay Hamlin
2020-02-18 Updated V2 design README.md for Jay Hamlin's design board/V2 folder
2020-02-18 updated BOM with latest Digikey prices
2020-02-18 updated pcb pricing
2020-02-23 Updated README with current status
2020-02-23 V2 software works now with V1 board if V2BOARD option disabled in Makefile
2020-02-24 V2 design is now WORKING - See README.md Makefile options
2020-02-24 Updated README.md and sdcard/ss80-1.lif adding a simple disk test
2020-02-24 Upadted README
2020-02-24 Updated IFC checking to clear bus faster - sdcard notes in README
2020-02-24 sdcard notes
2020-02-24 sdcard notes in README.md
2020-02-26 sdcard added RWTEST ASCII basic program copy/purge test files between units
2020-02-27 Updated README.md added configuration notes, gpib code using BOARD == value conditionals in code
2020-02-27 Updated BAUD settings to 115200 Baud and miniterm script - boot-trace.txt flash and bootup messages
2020-03-02 Updated all LIF images in sdcard created tools to make them automatically
2020-03-02 Updated README to document importing and exporting plain text files. redid all sdcard documenation
2020-03-02 Updated amigo.cfg file typo
2020-03-02 amigo.cfg typo
2020-03-02 Add a file with the program and library version I am using for development
2020-03-04 Major README.md rewrite
2020-03-04 Added compiled firmware release folder
2020-03-05 Enabled LED1 and LED2 for testing
2020-03-06 changed SDcard SPI bufffers to 74ACT125 and 74LVC125
2020-03-06 Updated notice in source files
2020-03-06 updated credits
2020-03-07 fixed SDCArd pullups. set ftdi series R to 120R. board cleaanup
2020-03-07 adding -03 assembly drawing
2020-03-08 Adding support for SparkFun Serial/SPI/I2C LCD display
2020-03-08 updated LCD initialization to test for display
2020-03-09 Updated the release HEX files
2020-03-09 released versions of board files
2020-03-09 Jay updated his board files
2020-03-11 Created program mkcfg to build hpdisk.cfg drive entries with HPDir database, drive filenames now have address suffix
2020-03-12 Updated sdcard/mkcfg/mkcfg.c to created disk configurations from the HPDir project config files
2020-03-14 Updated mkcfg to use computed LIF directory size, update sdcard/scripts/create_everything.sh to use it
2020-03-14 Sync with new board files from Jay
2020-03-14 new assembly drawing for march 15 release
2020-03-19 adding the enclosure cad file
2020-03-20 updated the release folder
2020-03-21 hpdisk.cfg disk definitions simpilified - we can use parameters from the HPDir project hpdir.ini file Now you only have to specify a model name, ppr and address and file for known drives
2020-03-24 Updated B4 as LED2 and C7 as CD
2020-03-24 Updated to make sure GPIO_B4 is enabled as an output BEFORE spi activity
2020-03-24 updated relase folder
2020-03-25 Added a delay after setting SS high prior to setting MSTR in spi controller register, added more comments
2020-03-25 really making sure sure the release/build was upto date
2020-03-25 Added SPI bus App note AVR151 to Documents/CHIPS, added yet mote notes to SPI initialization code
2020-03-25 Fixed initialization issue in SPI0_Init MUST set MSTR before SPE for SS to behave correctly
2020-03-29 Updating centroids file to release 03b
2020-03-30 updated position of init_timers() in main to after rs232 configuration
2020-03-30 updated release folder
2020-03-31 optiboot and make help
2020-04-01 changed Dives to Drives
2020-04-01 Added software reset keyword "reset"
2020-04-04 Added STK500V1/2 uploader for standalone flashing
2020-04-04 updated to work with python3
2020-04-04 Updated README flasher.py and added listports.py function to list ports on WIndows,Mac and Linux
2020-04-04 updated READme.md and uploader/README.md with flashing documenation
2020-04-06 Read_Config updated for code size reduction
2020-04-06 Updated flashing/compiling and connecting in README.md
2020-04-06 README.md flashing/compiling/connecting updates
2020-04-07 lif utility and Makefile updates
2020-04-08 Updated removed -static from standalone Makefil - Mac OS can not deal with it
2020-04-08 Added software installation script install_hp85disk.sh that also downloads the hp85disk V2 github sources
2020-04-08 install_hp85disk.sh notes
2020-04-08 Updated listports.py to detect serial sevices under Windows Ubuntu App
2020-04-08 Updated WSL install notes - added links
2020-04-08 Updated Makefile - using miniterm until miniterm.py hang issue solved under Windows WSL
2020-04-08 Updated serial terminal setup in README.md
2020-04-08 updated install_software.sh script
2020-04-09 Updated README.md cleaning up software install and updating notes
2020-04-09 README.md flashing and connecting updates
2020-04-09 Added config listing for Makefile, split stringup.c into two files so compiling mkcfg.c and lifsup.c standalone is easier to setup
2020-04-09 Added lib/parsing.c lib/parsing.h
2020-04-09 updated lib/parsing.c to include correct lib/parsing.h include
2020-04-09 README.md hp85disk help formatting
2020-04-09 hp85disk help commands formatting
2020-04-09 hp85disk README.md help formating
2020-04-09 README.md markdown
2020-04-09 Updated hp85disk command interface to accept upper or lower case commands
2020-04-09 Added note about Windows Store App
2020-04-10 Updated README.md layout
2020-04-10 README.md layout updates
2020-04-11 Updated README.md from V2 branch
2020-04-11 Updating master to V2 branch
2020-04-11 Updated master to V2 branch
2020-04-11 Updating master
2020-04-11 Updated master to V2
2020-04-11 updated pull
2020-04-11 Syncing master and V2
2020-04-11 Updated README.md to reference master branch
2020-04-11 updating V2 references
2020-04-11 Updated master
2020-04-11 Upadted README and install_hp85disk.sh script
2020-04-11 updating documents
2020-04-11 Getting rid of V2 branch references
2020-04-11 Updated installer
2020-04-11 cleaned up unused files
2020-04-11 Removed unused files
2020-04-11 edit
2020-04-11 edits
2020-04-11 Formatting and highlighting
2020-04-12 Updates to LIF documentation
2020-04-12 Updated to LIF documenation
2020-04-13 Updated lif comments
2020-04-13 README.md markdown issues
2020-04-13 Updated help menu processing
2020-04-14 Added notes on building an Arduino as ISP
2020-04-15 Makefile help edits
2020-04-17 Renamed AVRDUDE_PORT to ISP_PORT,AVRDUDE_SPEED to ISP_SPEED and PORT to HP85_PORT
2020-04-18 Added VERBOSE option to Makefile, compiles without warnings by adding attributes to arguments not yet used
2020-04-19 Makfile has verbose option - verbose is dsiabled by default but can be set make VERBOSE=1
2020-04-20 Code space reductions
2020-04-20 ran all code and header files throught bcpp
2020-04-20 Added SD Card detect code, LED2 is now error status, LED1 is activity status
2020-05-03 i2c code total rewrite, LCD display now updates at 10HZ
2020-05-03 update.last now contians the date and time of the last git commit
2020-05-03 LCD size changed to 2x16
2020-05-17 removed unused libraries - reduced flash usage
2020-05-18 moved unused code to unused directory, added %S format type to printf for strings in flash or using _memx pointers
2020-05-24 added backlight command for optional sparkfun serlcd display
2020-05-31 Added notes about status LEDs
2020-05-31 Updated requirements section
2020-05-31 Added summary for getting files into and out of the emulator SD card
2020-06-02 adding QuickStart guide
2020-06-03 flash updating README updates
2020-06-03 Fixed two typeos in Teledisk help message
2020-06-03 Updated teldisk_loader links
2020-06-03 Added HP85-IO.pdf
2020-06-03 lifutils.c LIF_DEBUG flag updated
2020-06-03 Added standalone desktop notes for lif td02lif and mkcfg commands
2020-06-04 Updated notes about WIndows python install
2020-06-04 Added a link to flasher.py, listports.py and gpib.hex
2020-06-04 Updated links to listportts.py, flasher.py and gpib.hex
2020-06-04 Updated documentation and links for listports.py, flasher.py and gpib.hex
2020-06-04 Updating reference links
2020-06-07 updated schematic with one with both pages
2020-06-09 Fixed multi-device support gpib_read_byte,gpib_write_byte,gpib_write_str fixed
2020-06-10 Updated user_task to clear the line buffer - update README
2020-06-10 README flashing update notes
2020-06-10 rs232 receive now masks upper bit
2020-06-11 I have added an user command input debugging option
2020-06-11 Added input debugging for displayinhg how arguments are being processed
2020-06-11 Doubled the string buffer for posix and fatfs test commands
2020-06-11 td02lif is not enabled in firmware - updated help messages
2020-06-11 fixed memory leak with fatfs_status and fatfs_scan_files
2020-06-13 Added warning about 20.04 Ubuntu App - stick with 18.04 fow now
2020-06-14 updated link to release/windows
2020-06-14 release/windows/README.md avrdude notes
2020-06-15 Updated release/windows/README.md
2020-06-15 release/windows/README.md updates
2020-06-16 update release files make sure using default 115200 baud
2020-06-17 mount and umount now update the drive count on the LCD
2020-06-17 mount,umount commands added, display updates drive count, README update
2020-06-17 fatfs help message missing from help
2020-06-17 updated drives_help menu and related text in README.md
2020-06-18 restored missing fatfs help from main help menu
2020-06-18 just making sure release folder is synced with updates
2020-06-19 removed plot help from gpib - we only do plot capture - it is automatic, removed mmc_init and mmc_test ment tests
2020-06-21 help menu updates, update safefree and mem statistics code
2020-06-24 lifutils.c allow $ character, make sectorsize != 256 a warning
2020-07-07 Updated lifutilities to allow all characters except '.:"'
2020-07-07 updated lifutils to only prohibit dot.colon,quotes, /. \ and <32 or > 127
2020-07-08 Removed Tindie store references
2020-07-08 added lif renamevol - volume rename function

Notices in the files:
README.md:
(c) 2014-2020 by Mike Gore
parts and their libraries:
SparkFun-Connectors: Licensing: CC v3.0 Share-Alike You are welcome to use this library for commercial purposes.
SparkFun-Electromechanical: Licensing: Creative Commons ShareAlike 4.0 International - https://creativecommons.org/licenses/by-sa/4.0
